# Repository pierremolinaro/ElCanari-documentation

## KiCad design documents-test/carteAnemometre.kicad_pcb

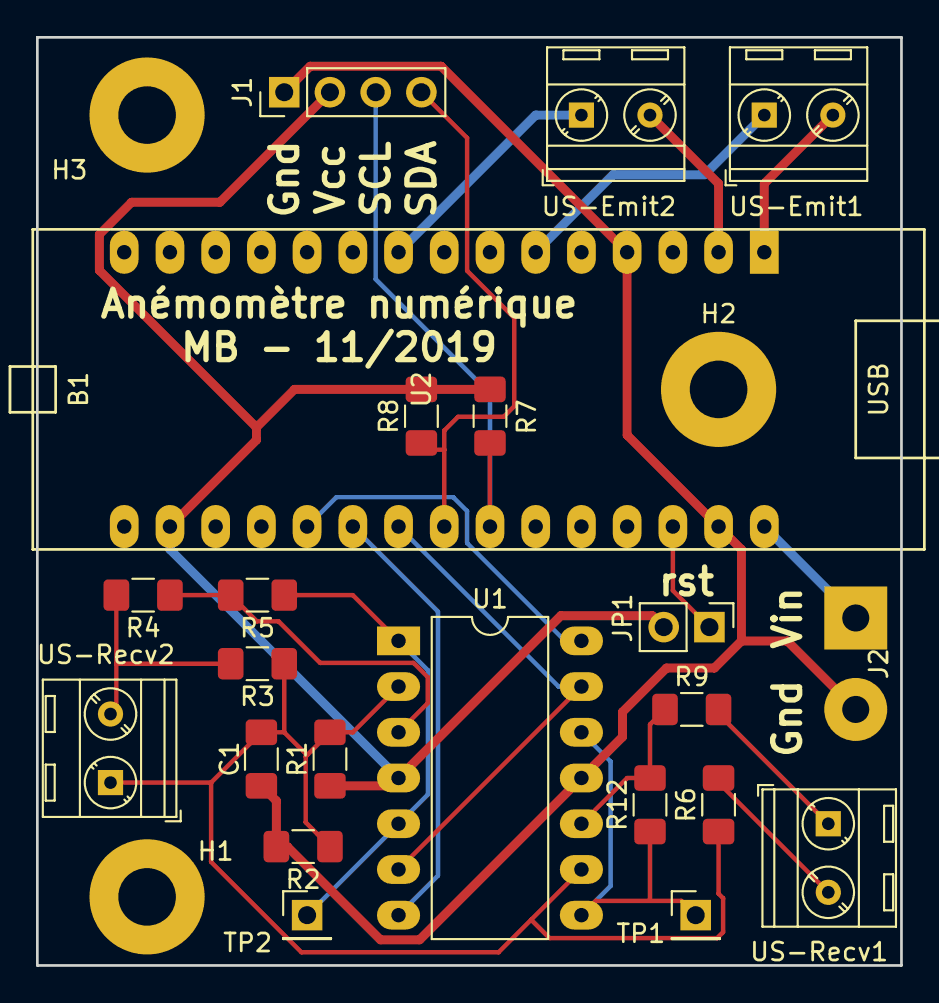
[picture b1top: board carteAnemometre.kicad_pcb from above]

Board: 2 copper layers, 48.0 x 51.6 mm, 25 parts (0 on the bottom side), 21 nets.

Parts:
C1: 100n; C_1206_3216Metric_Pad1.42x1.75mm_HandSolder
H1, H2, H3: MountingHole; MountingHole_3.2mm_M3_Pad
J1: Conn_01x04_Male; PinHeader_1x04_P2.54mm_Vertical
J2: Conn_01x02_Female; SolderWirePad_1x02_P5.08mm_Drill1.5mm
JP1: Jumper; PinHeader_1x02_P2.54mm_Vertical
R1, R2: 1K; R_1206_3216Metric_Pad1.42x1.75mm_HandSolder
R3, R4, R6, R9: 3.9K; R_1206_3216Metric_Pad1.42x1.75mm_HandSolder
R5, R12: 1M; R_1206_3216Metric_Pad1.42x1.75mm_HandSolder
R7, R8: 4.7K; R_1206_3216Metric_Pad1.42x1.75mm_HandSolder
TP1, TP2: TestPoint; PinHeader_1x01_P2.54mm_Vertical
U1: MCP6L94; DIP-14_W10.16mm_LongPads
U2: Nucleo-L432KC; nucleo-F303k8
US-Emit1, US-Emit2: Speaker_Ultrasound; TerminalBlock_MetzConnect_Type086_RT03402HBLC_1x02_P3.81mm_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
US-Recv1, US-Recv2: Speaker_Ultrasound; TerminalBlock_MetzConnect_Type086_RT03402HBLC_1x02_P3.81mm_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

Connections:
/ECHO1: U1.7, U2.21
/ECHO2: U1.14, U2.20
/GND_US: C1.1, R1.2, R2.1, R3.1, R6.1, U1.2, U1.9, US-Recv2.1
/I2C_SCL: J1.3, R7.1, U2.24
/I2C_SDA: J1.4, R8.1, U2.23
/SENSIB: U1.6, U1.13, U2.22
/TRIG1+: U2.2, US-Emit2.2
/TRIG1-: U2.9, US-Emit2.1
/TRIG2+: U2.6, US-Emit1.1
/TRIG2-: U2.1, US-Emit1.2
/Vin: J2.1, U2.30
GND: C1.2, J1.1, J2.2, R2.2, U1.11, U2.4, U2.29
unnamed: JP1.1, U2.28
unnamed: R3.2, R4.2, US-Recv2.2
unnamed: R4.1, R5.2, U1.3
unnamed: R5.1, TP2.1, U1.1, U1.5
unnamed: R6.2, US-Recv1.2
unnamed: R9.2, US-Recv1.1
unnamed: R12.1, TP1.1, U1.8, U1.12
unnamed: R9.1, R12.2, U1.10
VCC: J1.2, JP1.2, R1.1, R7.2, R8.2, U1.4, U2.17

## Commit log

2019-10-15 Ajout fichiers
2019-10-17 Ajout projets contraintes
2019-10-17 Suite
2019-10-20 Custom Stack views
2020-09-13 Ajout icônes ElCanari, documentation Apple.
2020-11-13 Amélioration curseurs
2020-11-13 Ajout projet essai ui
2020-11-29 Nouveau projet essai contraintes sans IB
2021-01-31 Suite projet contraintes sans IB
2021-02-01 Utilisation NSStackView
2021-02-21 Nouvelle tentative AutoLayout
2021-03-02 Property Wrapper
2021-04-14 documents test
2021-04-15 Ajout package test
2021-06-25 Ajout documents exemples
2021-06-28 Ajout dessin artwork
2021-07-23 Fichiers d'exemple
2022-09-20 MAJ essai gerber
2023-11-19 Ajout docs Gerber
2024-05-31 Ajout doc Gerber et Excellon
2024-08-11 Exemple grid-view
2025-01-11 Suppression fichiers transférés dans ELCanariDev
